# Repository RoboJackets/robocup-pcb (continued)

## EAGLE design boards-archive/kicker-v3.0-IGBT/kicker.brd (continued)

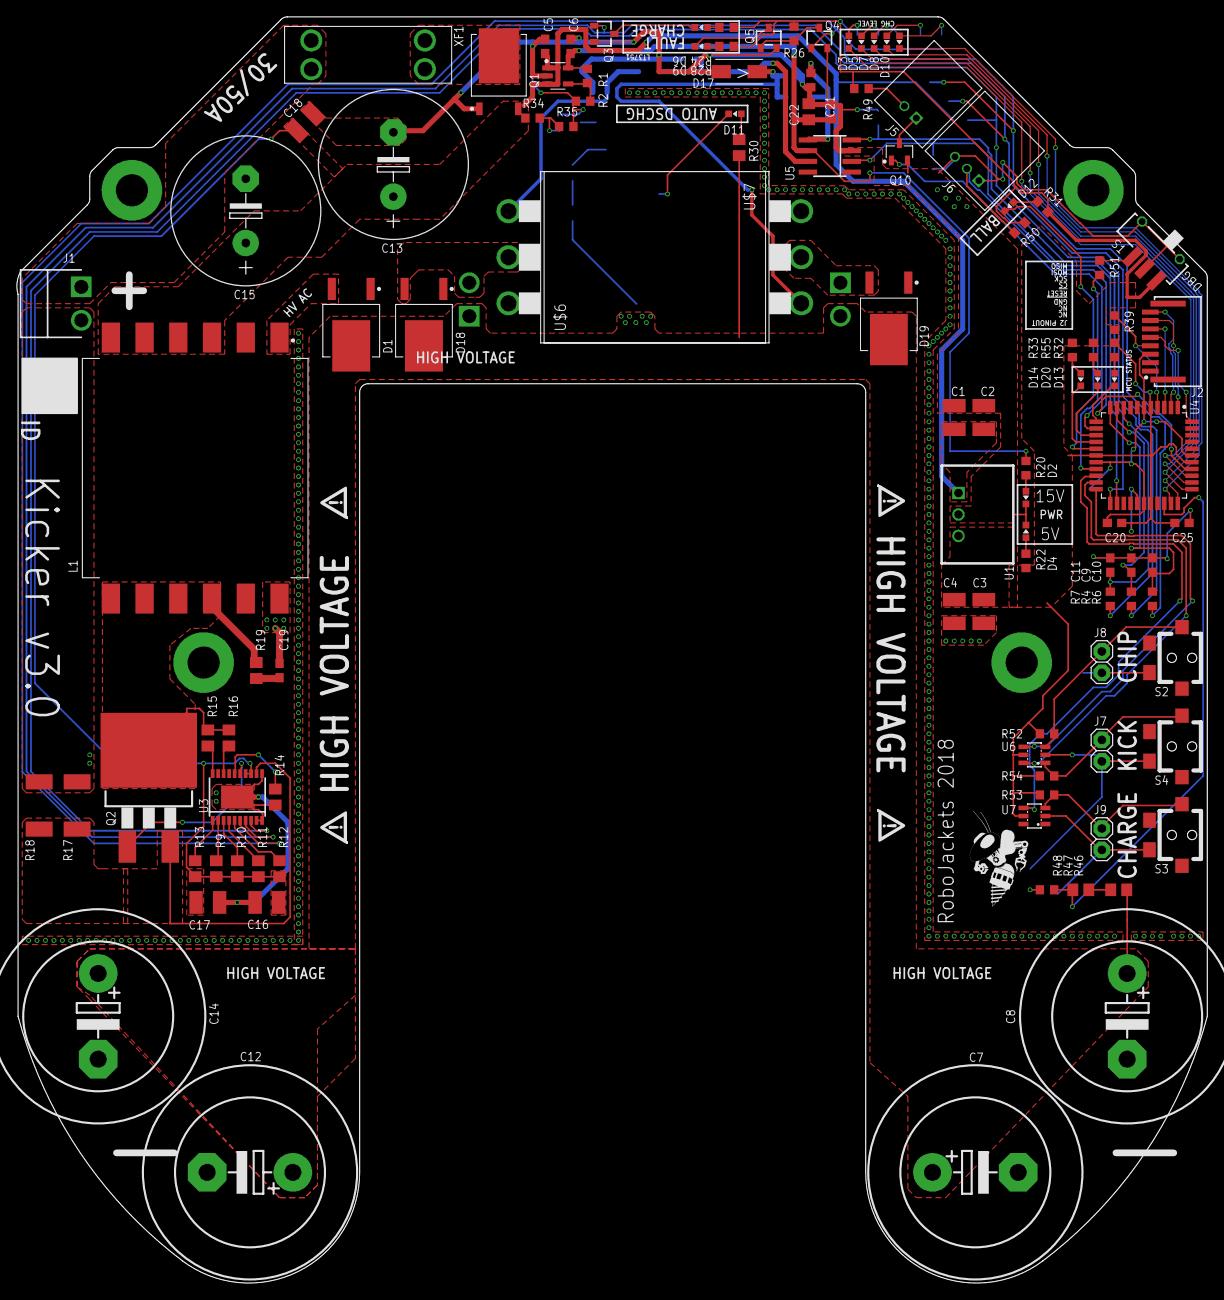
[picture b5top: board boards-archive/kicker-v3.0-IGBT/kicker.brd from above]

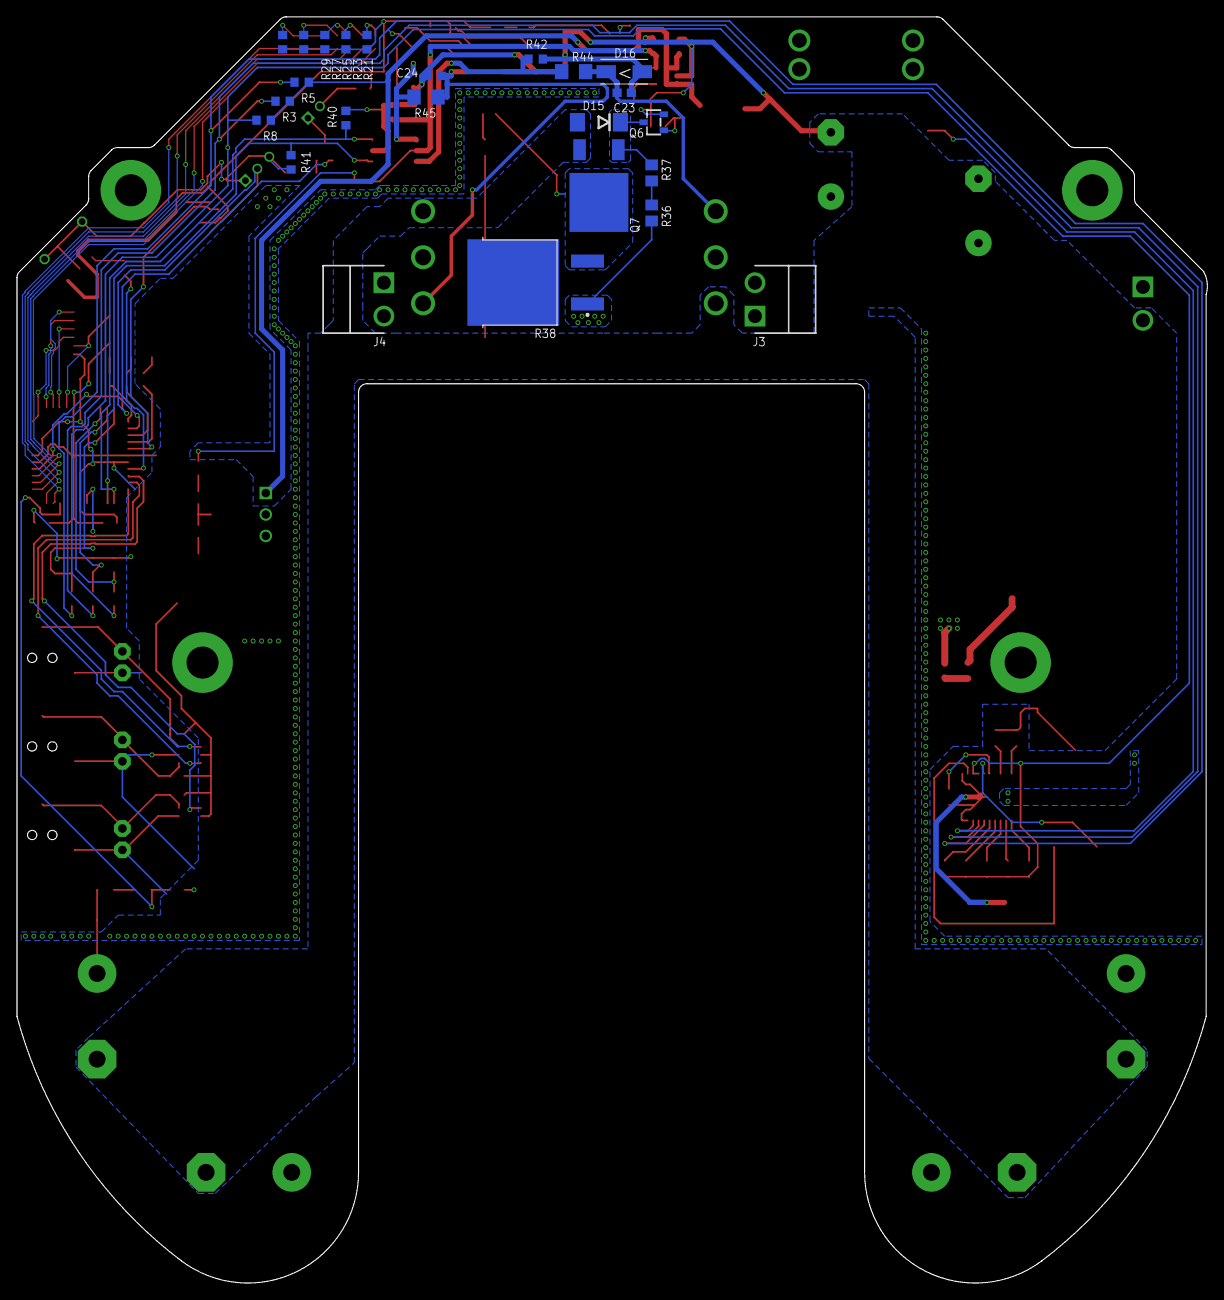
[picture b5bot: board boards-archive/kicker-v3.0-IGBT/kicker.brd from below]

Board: 2 copper layers, 141.1 x 150.1 mm, 137 parts (24 on the bottom side), 84 nets.

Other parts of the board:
U$1, U$2, U$3, U$4: WARNING2
U$5: ROBOBUZZ_0.6X
